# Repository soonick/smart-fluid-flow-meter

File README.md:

# Smart Fluid Flow Meter

Hardware and software for a system that monitors flow of fluids (most likely water) and reports it to a back-end that can emit alerts based on configured preferences.

- [backend](/backend/) - Contains the back end server where measurements will be posted
- [case](/case/) - 3d model of the PCB case
- [esp32](/esp32/) - The ESP32 code that takes care of reading the sensor and posting measurements to the back-end
- [frontend](/frontend/) - The front end that can be used to manage accounts and devices
- [kicad](/kicad/) - Electronic circuit schematic

## User documentation

### LED indicators

- **Yellow** - Device is booting
- **Green, yellow and red** - Device set to factory settings and waiting for configuration (See below for instructions to configure)
- **Green** - Device is configured and behaving correctly
- **Green and yellow** - Device is in the middle of sending a request to the back-end
- **Red** - Last request to back-end failed. This could be because configuration is incorrect, or the configured modem is unreachable
- **None** - This should not happen, it means something is very wrong

### Configuration

When the device is in factory settings (Green, yellow and red LEDs on), the ESP32 will start an access point named `my-esp32-ssid`. Connect to the access point using the password `APassword`.

Once connected, navigate to the url: `sffm.mekadomus.com`. You should get a screen like the following:

<config screen>

Fill the data as follows:
- *Wifi Network* - The name of the network the device will connect to
- *Wifi Password* - The password for the given SSID
- *Device key* - The unique identifier for this device. This ID will be validated by the backend, so it must be a valid one

After submitting the form, you should get the following confirmation screen:

The device will proceed to disable the access point and will start reading measurements from the sensor and sending them to the backend every  `MS_BETWEEN_POSTS`.

### Factory reset

If you need to re-configure the device, press and hold the device button for 5 seconds. After some time the green, yellow and red LEDs should all turn on.

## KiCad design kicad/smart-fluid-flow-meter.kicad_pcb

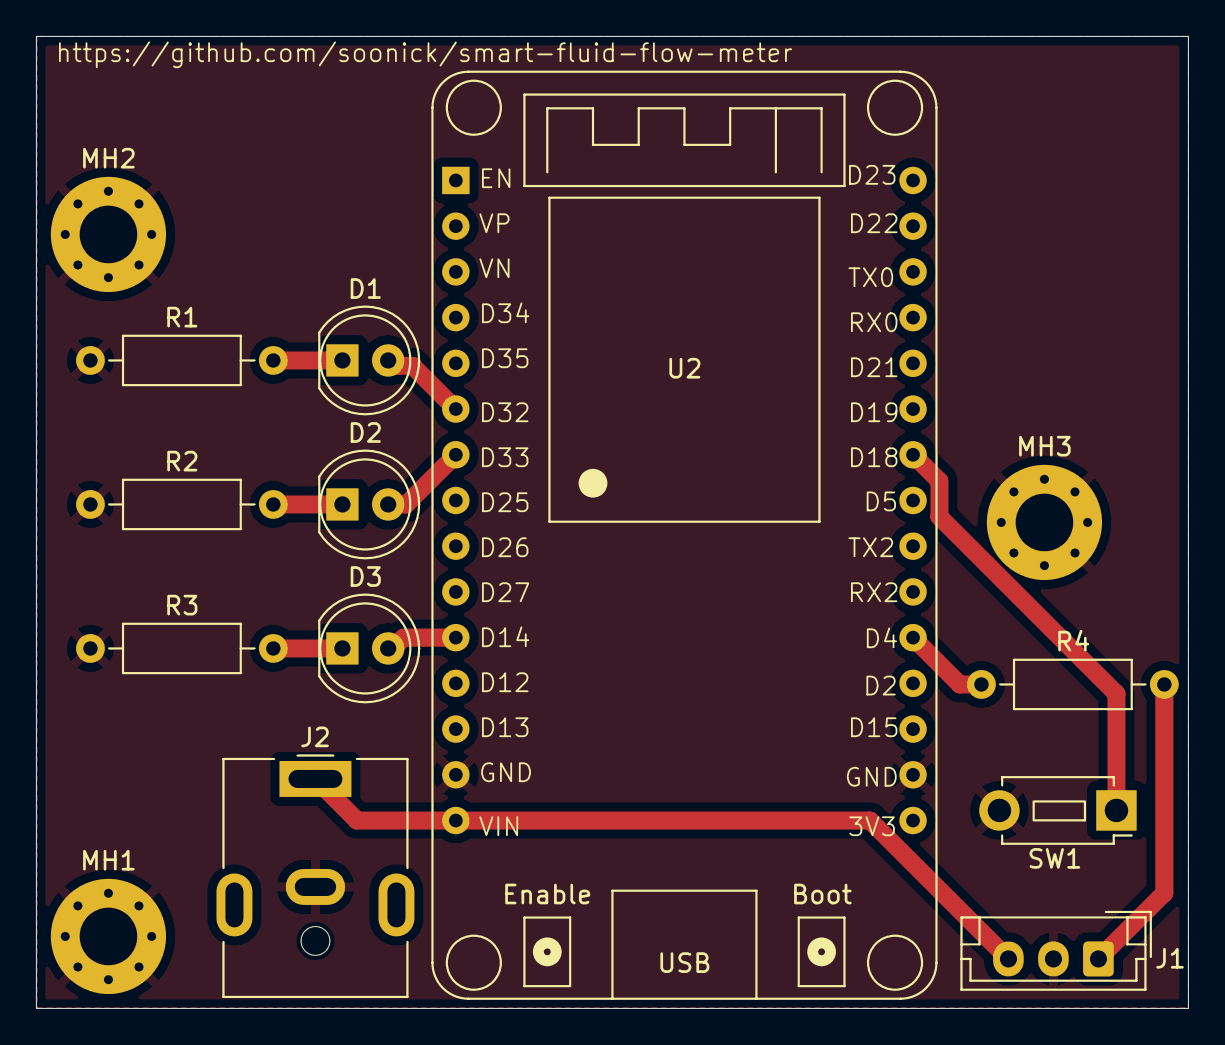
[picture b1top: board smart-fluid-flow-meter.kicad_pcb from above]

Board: 2 copper layers, 64.0 x 54.0 mm, 14 parts (0 on the bottom side), 11 nets.

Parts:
D1: Green LED; LED_D5.0mm
D2: Yellow LED; LED_D5.0mm
D3: Red LED; LED_D5.0mm
J1: YF-S201; JST_EH_B3B-EH-A_1x03_P2.50mm_Vertical
J2: Barrel_Jack; BarrelJack_CUI_PJ-063AH_Horizontal
MH1, MH2, MH3: MountingHole_Pad; MountingHole_3.2mm_M3_Pad_Via
R1, R3: 220; R_Axial_DIN0207_L6.3mm_D2.5mm_P10.16mm_Horizontal
R2: 100; R_Axial_DIN0207_L6.3mm_D2.5mm_P10.16mm_Horizontal
R4: 3.3M; R_Axial_DIN0207_L6.3mm_D2.5mm_P10.16mm_Horizontal
SW1: Factory reset button; SW_PUSH_1P1T_6x3.5mm_H4.3_APEM_MJTP1243
U2: ESP32-DevkitV1; esp32_devkit_v1

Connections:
0: J1.2, J2.2, MH1.1, MH2.1, MH3.1, R1.1, R2.1, R3.1, SW1.2, U2.2 (GND), U2.29 (GND)
unnamed: D1.2 (A), U2.21 (D32)
unnamed: D1.1 (K), R1.2
unnamed: D2.2 (A), U2.22 (D33)
unnamed: D2.1 (K), R2.2
unnamed: D3.2 (A), U2.26 (D14)
unnamed: D3.1 (K), R3.2
unnamed: J1.1, R4.2
unnamed: J1.3, J2.1, U2.30 (VIN)
unnamed: R4.1, U2.5 (D4)
unnamed: SW1.1, U2.9 (D18)

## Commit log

2024-04-07 Shell for rust backend. Fixes #1
2024-04-09 Endpoint that receives measures. Fixes #2
2024-04-10 Return custom errors on failures. Fixes #7
2024-04-10 Split project into different modules and folders. Fixes #9
2024-04-10 Save measurements to MySQL database. Fixes #4
2024-04-11 Save measurementes to firestore. Fixes #5
2024-04-12 Containerize. Fixes: #3
2024-04-12 Add start instructions to README
2024-04-12 Update AppState to not use generics. #10
2024-04-12 Invalid json input integration test. #10
2024-04-12 Integration tests for save_measure enpoint. #10
2024-04-13 Test the response when there is a DB error. #10
2024-04-14 Integration test for MySQL. #10
2024-04-17 Integration test for Firestore. Fixes #10
2024-04-17 Create make target verify. Checks format and runs tests. #11
2024-04-18 Circleci. Fixes #11
2024-04-18 Configuration management. Fixes #6
2024-04-18 Watch repo por changes and recompile when running locally. Fixes #12
2024-04-18 Log all requests. Fixes: #8
2024-04-18 Arduino sketch skeleton. Fixes #13
2024-04-18 read flow from sensor
2024-04-18 Build Arduino Sketch on CI. Fixes #15
2024-04-18 Add README file with CI status. Fixes #16
2024-04-19 Code formatting in CI. Fixes #20
2024-04-27 Build sketch using makefile. Fixes #21
2024-04-28 Fix make upload
2024-04-28 Move source for sketch to src/ folder
2024-04-28 Fix make verify
2024-05-06 Migrate sketch to use CMake. Fixes #23
2024-05-09 Container with vim for sketch development. Fixes #22
2024-05-11 Include Arduino.h in main.cpp
2024-05-11 Update makefile and dev dockerfile to minimize image re-builds
2024-05-13 Fix vim LSP
2024-05-15 Setup for unit testing. Fixes #24
2024-06-09 Add r4-wifi-manager dependency
2024-06-09 Update all submodules before running checks in circle ci
2024-06-22 Save wifi details in eeprom
2024-06-25 Bump r4-wifi-manager
2024-06-26 Only start access point if userConfig doesn't exist
2024-06-28 Reset device settings if button is long pressed
2024-07-05 Connect to WiFi once board is correctly set up
2024-07-07 Read flow from sensor. Fixes #17
2024-07-07 Fix fluid meter singleton
2024-07-09 Publish backend image to GCR
2024-07-11 Move configuration to environment variables. #27
2024-07-12 Use DB migrations to create DB. #27
2024-07-14 Add instructions for running production version locally. #27
2024-07-14 Allow circleci to run in all branches
2024-07-14 Allow circleci to run in all branches (#30)
2024-07-14 Health check endpoint. #27
2024-07-14 Health check endpoint. #27 (#31)
2024-07-18 Add instructions for releasing backend
2024-07-19 Fix `id` not being populated by when using firestore. Fixes #28
2024-07-20 Fix `id` not being populated by when using firestore. Fixes #28 (#32)
2024-07-20 Create make vim command for backend. Fixes #29
2024-07-20 Create make vim command for backend. Fixes #29 (#33)
2024-07-22 Don't require date for measure endpoint. #18
2024-07-22 Don't require date for measure endpoint. #18 (#35)
2024-07-23 [sketch] Post sensor data to the backend. Fixes #18
2024-07-23 [sketch] Post sensor data to the backend. Fixes #18 (#37)
2024-07-23 [sketch] Add led on indicator. #26
2024-07-23 [sketch] Fix littersMemory type
2024-07-23 [sketch] Add led on indicator. #26 (#38)
2024-07-23 [sketch] Fix littersMemory type (#39)
2024-08-06 Add folder for ESP with blink example
2024-08-06 Add folder for ESP with blink example (#40)
2024-10-01 Get latest r4-wifi-manager
2024-10-01 Get latest r4-wifi-manager (#45)
2024-10-01 Upgrade ESP-IDF
2024-10-01 Upgrade ESP-IDF (#44)
2024-10-01 [esp32] Treat all warnings as errors
2024-10-01 [esp32] Treat all warnings as errors (#46)
2024-10-01 [esp32] First commit for wifi-manager. Sets up AP and serves hello world
2024-10-01 [esp32] First commit for wifi-manager. Sets up AP and serves hello world (#47)
2024-10-30 Simple usage of esp-idf-wifi-manager
2024-10-30 Simple usage of esp-idf-wifi-manager (#48)
2024-11-01 Update main readme. Remove sketch link, add esp32 link
2024-11-01 Update main readme. Remove sketch link, add esp32 link (#50)
2024-11-01 Created kicad folder
2024-11-01 Created kicad folder (#51)
2024-11-02 Add power LED and yf-s201 to kicad schematic
2024-11-02 Power LED
2024-11-02 Add power LED and yf-s201 to kicad schematic (#52)
2024-11-02 Power LED (#49)
2024-11-05 [esp32] Move source code to src folder
2024-11-05 [esp32] Move source code to src folder (#53)
2024-11-09 Add resistors to water flow meter in schematic. Add notes to schematic
2024-11-09 Add resistors to water flow meter in schematic. Add notes to schematic (#54)
2024-11-09 Replace 6 1MOhm resistors with 2 3.3MOhm resistors in schematic
2024-11-10 Replace 6 1MOhm resistors with 2 3.3MOhm resistors in schematic (#55)
2024-11-10 Add factory reset button
2024-11-10 Add factory reset button (#56)
2024-11-10 Turn on power LED
2024-11-10 Turn on power LED (#57)
2024-11-11 Bump esp-idf-wifi-manager
2024-11-11 Bump esp-idf-wifi-manager (#58)
2024-11-11 Bump esp-idf-wifi-manager (#59)
2024-11-12 Upgrade esp-idf-wifi-manager
2024-11-12 Upgrade esp-idf-wifi-manager (#60)
2024-11-12 Shutdown AP after getting config. Restart AP after factory reset
2024-11-12 Shutdown AP after getting config. Restart AP after factory reset (#61)
2024-11-12 [esp32] Read measurements from flow meter
2024-11-13 [esp32] Read measurements from flow meter (#62)
2024-11-20 Send measurements to backend. Fixes #43
2024-11-20 Send measurements to backend. Fixes #43 (#63)
2024-11-20 Add status LEDs to kicad. #26
2024-11-20 Add status LEDs to kicad. #26 (#70)
2024-11-20 Add spice model propererties to some symbols
2024-11-20 Add spice model propererties to some symbols (#71)
2024-11-22 Design PCB
2024-11-22 Design PCB (#74)
2024-11-22 Remove smart-fluid-flow-meter folder inside of kicad folder
2024-11-22 Remove smart-fluid-flow-meter folder inside of kicad folder (#75)
2024-11-25 [esp32] Move backend URL to constant
2024-11-25 [esp32] Move backend URL to constant (#78)
2024-11-25 LEDs turn in different ways depending on the state of the system. Fixes #26
2024-11-25 LEDs turn in different ways depending on the state of the system. Fixes #26 (#79)
2024-11-25 Remove sketch folder. We use ESP32 now
2024-11-25 Remove sketch folder. We use ESP32 now (#81)
2024-11-25 Retry request if it fails. Fixes #80
2024-11-25 Retry request if it fails. Fixes #80 (#82)
2024-11-27 Add user documentation to README. Fixes #76
2024-11-27 Add user documentation to README. Fixes #76 (#84)
2024-11-27 Make sure litters information if persisted if network request fails. Fixes #65
2024-11-27 Make sure litters information if persisted if network request fails. Fixes #65 (#85)
2024-11-27 Remove unnecessary TODOs. Fixes #68
2024-11-27 Remove unnecessary TODOs. Fixes #68 (#86)
2024-11-27 Fix Electrical Rules Checker errors. Fixes #73
2024-11-27 Fix Electrical Rules Checker errors. Fixes #73 (#87)
2024-11-27 Wider traces and ground plane. #77
2024-11-27 Wider traces and ground plane. #77 (#88)
2024-11-28 [backend] Upgrade rust
2024-11-28 [backend] Upgrade rust (#90)
2024-11-28 [kicad] Use the gnd plane for gnd connections
2024-11-28 [kicad] Use the gnd plane for gnd connections (#89)
2024-11-28 [kicad] Update gerbers
2024-11-28 [kicad] Update gerbers (#91)
2024-12-02 First prototype of bottom case. #92
2024-12-02 First prototype of bottom case. #92 (#93)
2024-12-03 First prototype of top case. #92
2024-12-03 Remove gerbers since they can be generated from pcb design file
2024-12-03 First prototype of top case. #92 (#94)
2024-12-03 Remove gerbers since they can be generated from pcb design file (#95)
2024-12-03 Add holes to top cover. #92
2024-12-03 Add holes to top cover. #92 (#96)
2024-12-04 Create windows for led pipes. #92
2024-12-04 Create windows for led pipes. #92 (#97)
2024-12-05 [case] Button extension. Fixes #99
2024-12-05 [case] Button extension. Fixes #99 (#102)
2024-12-06 [case] Clips for securing to and bottom together. Fixes #98
2024-12-06 [case] Clips for securing to and bottom together. Fixes #98 (#103)
2024-12-06 [esp32] Bump wifi-manager. Fixes #104
2024-12-06 [esp32] Bump wifi-manager. Fixes #104 (#105)
2024-12-06 Fix readme formatting
2024-12-06 Fix readme formatting (#106)
2024-12-07 [case] Update holes to match received parts
2024-12-07 [case] Update holes to match received parts (#112)
2024-12-07 [frontend] Basic sveltekit app skeleton. Fixes #108
2024-12-07 [frontend] Basic sveltekit app skeleton. Fixes #108 (#114)
2024-12-15 [case] Create folder for indoor case. Made modifications and added assembly section
2024-12-15 [case] Create folder for indoor case. Made modifications and added assembly section (#116)
2024-12-16 [backend] Update telescope ignored in vim image
2024-12-16 [backend] Update telescope ignored in vim image (#117)
2024-12-16 [backend] Build cloudflare client. #107
2024-12-16 [backend] Build cloudflare client. #107 (#118)
2024-12-26 [esp32] Tune flow sensor conversion factor
2024-12-26 [esp32] Tune flow sensor conversion factor (#120)
2024-12-26 [case] Update some measurements so case closes more easily
2024-12-26 [case] Update some measurements so case closes more easily (#121)
2024-12-28 [backend] Discard duplicate measurements sent by clients. Fixes #123
2024-12-28 [backend] Discard duplicate measurements sent by clients. Fixes #123 (#125)
2024-12-28 Fix CI publish step
2024-12-28 Fix CI publish step (#127)
2024-12-28 [backend] Add logs to debug duplicate measures. #123
2024-12-28 [backend] Add logs to debug duplicate measures. #123 (#129)
2024-12-28 [backend] Don't add files to dev docker image so it doesn't have to rebuild every time. Fixes #119
2024-12-28 [backend] Don't add files to dev docker image so it doesn't have to rebuild every time. Fixes #119 (#130)
2024-12-28 [backend][esp32] Rename measure to measurement. Fixes #131
2024-12-28 [backend][esp32] Rename measure to measurement. Fixes #131 (#132)
2024-12-28 [backend] When using firestore use a document-id based on device id and timestamp to prevent duplicates. Fixes #123
2024-12-29 [backend] When using firestore use a document-id based on device id and timestamp to prevent duplicates. Fixes #123 (#133)
2024-12-30 [backend] Sign-up. #107
2024-12-30 [backend] Sign-up. #107 (#135)
2024-12-31 [esp32] Release http request semaphore even if we can't get an IP. Fixes #134
2024-12-31 [esp32] Release http request semaphore even if we can't get an IP. Fixes #134 (#136)
2024-12-31 [frontend] Simple login form. #107
2024-12-31 [frontend] Simple login form. #107 (#138)
2024-12-31 [frontend] Add CI fro frontend. Fixes #115
2024-12-31 [frontend] Add CI fro frontend. Fixes #115 (#139)
2024-12-31 [frontend] Validate password with zxcvbn. #107
2024-12-31 [frontend] Validate password with zxcvbn. #107 (#141)
2024-12-31 [frontend] Fix build warnings. #107
2024-12-31 [frontend] Fix build warnings. #107 (#142)
2024-12-31 [frontend] Add make vim command. Fixes #140
2024-12-31 [frontend] Add make vim command. Fixes #140 (#143)
2025-01-02 Use mekadomus as domain name for backend
2025-01-02 Use mekadomus as domain name for backend (#144)
2025-01-02 Use mekadomus as domain name for backend (#145)
2025-01-02 Update circleci deploy key fingerprint
2025-01-02 Update circleci deploy key fingerprint (#146)
2025-01-02 Update backend prod image name
2025-01-02 Update backend prod image name (#147)
2025-01-03 [backend] Add captcha secret to .env.sample
2025-01-03 [backend] Add captcha secret to .env.sample (#148)
2025-01-03 [kicad] Make esp32 holes larger. Fixes #122
2025-01-03 [kicad] Make esp32 holes larger. Fixes #122 (#149)
2025-01-03 [frontend] Add turnstile to login form. #107
2025-01-03 [frontend] Add turnstile to login form. #107 (#150)
2025-01-03 [frontend] Publish frontend to artifact registry. Fixes #151
2025-01-03 [frontend] Publish frontend to artifact registry. Fixes #151 (#152)
2025-01-03 [frontend] Use env varible for backend url. #153
2025-01-03 [frontend] Use env varible for backend url. #153 (#154)
2025-01-03 [backend] Add v1 prefix to endpoints. #153
2025-01-04 [backend] Add v1 prefix to endpoints. #153 (#155)
